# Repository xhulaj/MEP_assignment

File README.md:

##tvoja mama ma rit jak stodolu

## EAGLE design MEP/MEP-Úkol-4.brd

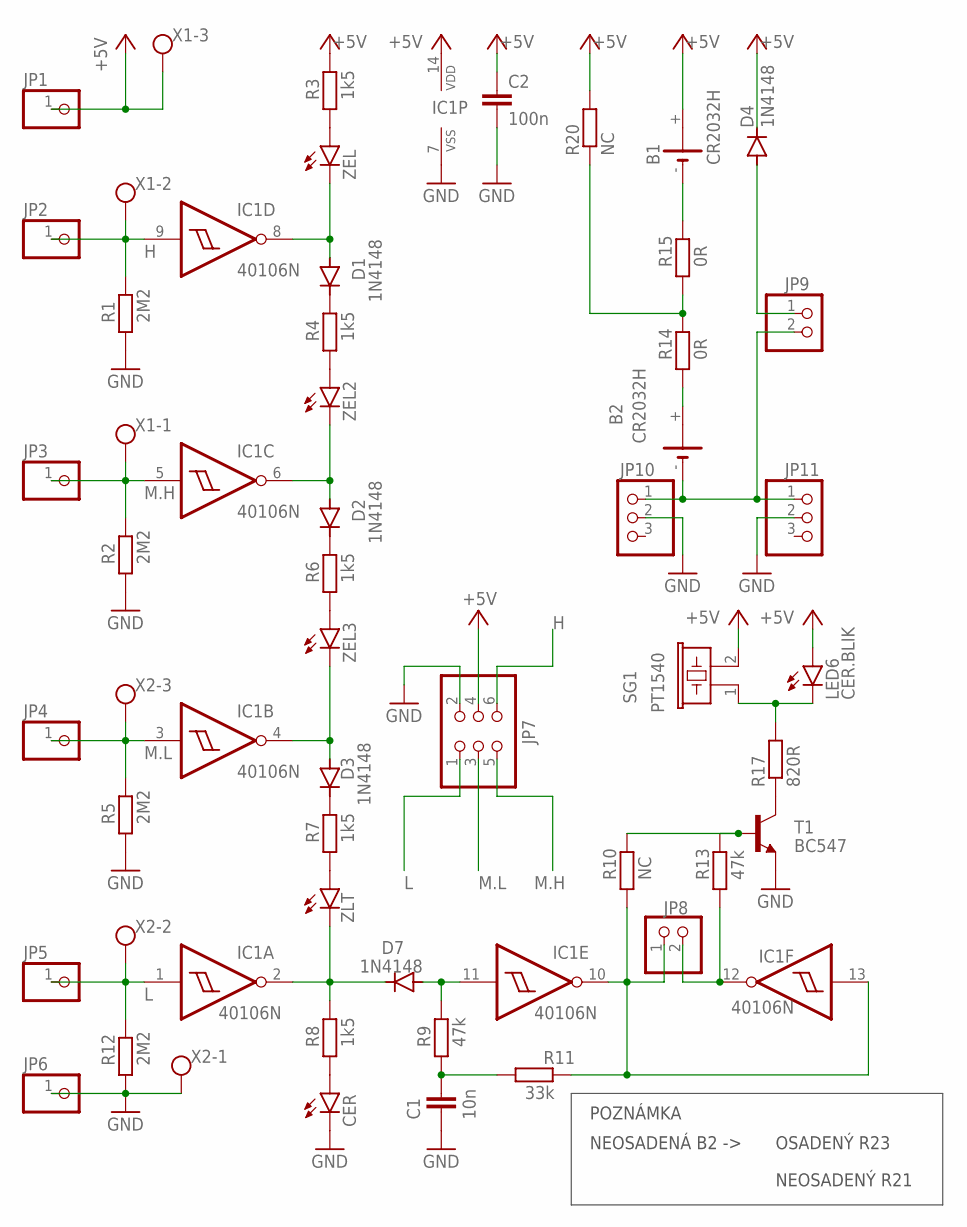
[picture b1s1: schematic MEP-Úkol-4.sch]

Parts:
B1, B2: CR2032H
C1: 10n; C0805
C2: 100n; C0805
CER: LEDCHIP-LED0805; CHIP-LED0805
D1, D2, D3, D4, D7: 1N4148; DO35-7
IC1: 40106N; DIL14
JP1, JP2, JP3, JP4, JP5, JP6: PINHD-1X1; 1X01
JP7: PINHD-2X3; 2X03
JP8, JP9: PINHD-1X2; 1X02
JP10, JP11: PINHD-1X3; 1X03
LED6: CER.BLIK; CHIP-LED0805
R1, R2, R5, R12: 2M2; R0805
R3, R4, R6, R7, R8: 1k5; R0805
R9, R13: 47k; R0805
R10, R20: NC; R0805
R11: 33k; R0805
R14, R15: 0R; R0805
R17: 820R; R0805
SG1: PT1540; EFBRD22C41
T1: BC547; SOT23-BEC
X1, X2: AK500/3
ZEL, ZEL2, ZEL3: LEDCHIP-LED0805; CHIP-LED0805
ZLT: LEDCHIP-LED0805; CHIP-LED0805

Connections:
+5V: B1.+, C2.1, D4.C, IC1.14 (VDD), JP1.1, JP7.4, LED6.A, R3.2, R20.2, SG1.2, X1.3
GND: C1.2, C2.2, CER.C, IC1.7 (VSS), JP6.1, JP7.2, JP10.2, JP11.2, R1.1, R2.1, R5.1, R12.1, T1.E, X2.1
H: IC1.9 (I), JP2.1, JP7.6, R1.2, X1.2
L: IC1.1 (I), JP5.1, JP7.1, R12.2, X2.2
M.H: IC1.5 (I), JP3.1, JP7.5, R2.2, X1.1
M.L: IC1.3 (I), JP4.1, JP7.3, R5.2, X2.3
unnamed: R3.1, ZEL.A
unnamed: R4.1, ZEL2.A
unnamed: D2.C, R6.2
unnamed: R6.1, ZEL3.A
unnamed: R7.1, ZLT.A
unnamed: CER.A, R8.1
unnamed: IC1.10 (O), IC1.13 (I), JP8.1, R10.1, R11.2
unnamed: D1.C, R4.2
unnamed: D1.A, IC1.8 (O), ZEL.C
unnamed: D2.A, IC1.6 (O), ZEL2.C
unnamed: IC1.12 (O), JP8.2, R13.1
unnamed: R10.2, R13.2, T1.B
unnamed: D3.A, IC1.4 (O), ZEL3.C
unnamed: R17.1, T1.C
unnamed: D3.C, R7.2
unnamed: LED6.C, R17.2, SG1.1
unnamed: D7.C, IC1.2 (O), R8.2, ZLT.C
unnamed: B2.-, JP9.2, JP10.1, JP11.1
unnamed: D7.A, IC1.11 (I), R9.2
unnamed: C1.1, R9.1, R11.1
unnamed: B2.+, R14.1
unnamed: R14.2, R15.1, R20.1
unnamed: B1.-, R15.2
unnamed: D4.A, JP9.1

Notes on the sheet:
POZNÁMKA
NEOSADENÁ B2 ->
OSADENÝ R23
NEOSADENÝ R21

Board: 2 copper layers, 48 parts (26 on the bottom side), 30 nets, no tracks yet.

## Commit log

2020-10-21 initial D
2020-10-21 endmysuffering
